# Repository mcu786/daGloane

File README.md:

daGloane
========

daGloane is a quadcopter with a takeoff mass of less than 50grams

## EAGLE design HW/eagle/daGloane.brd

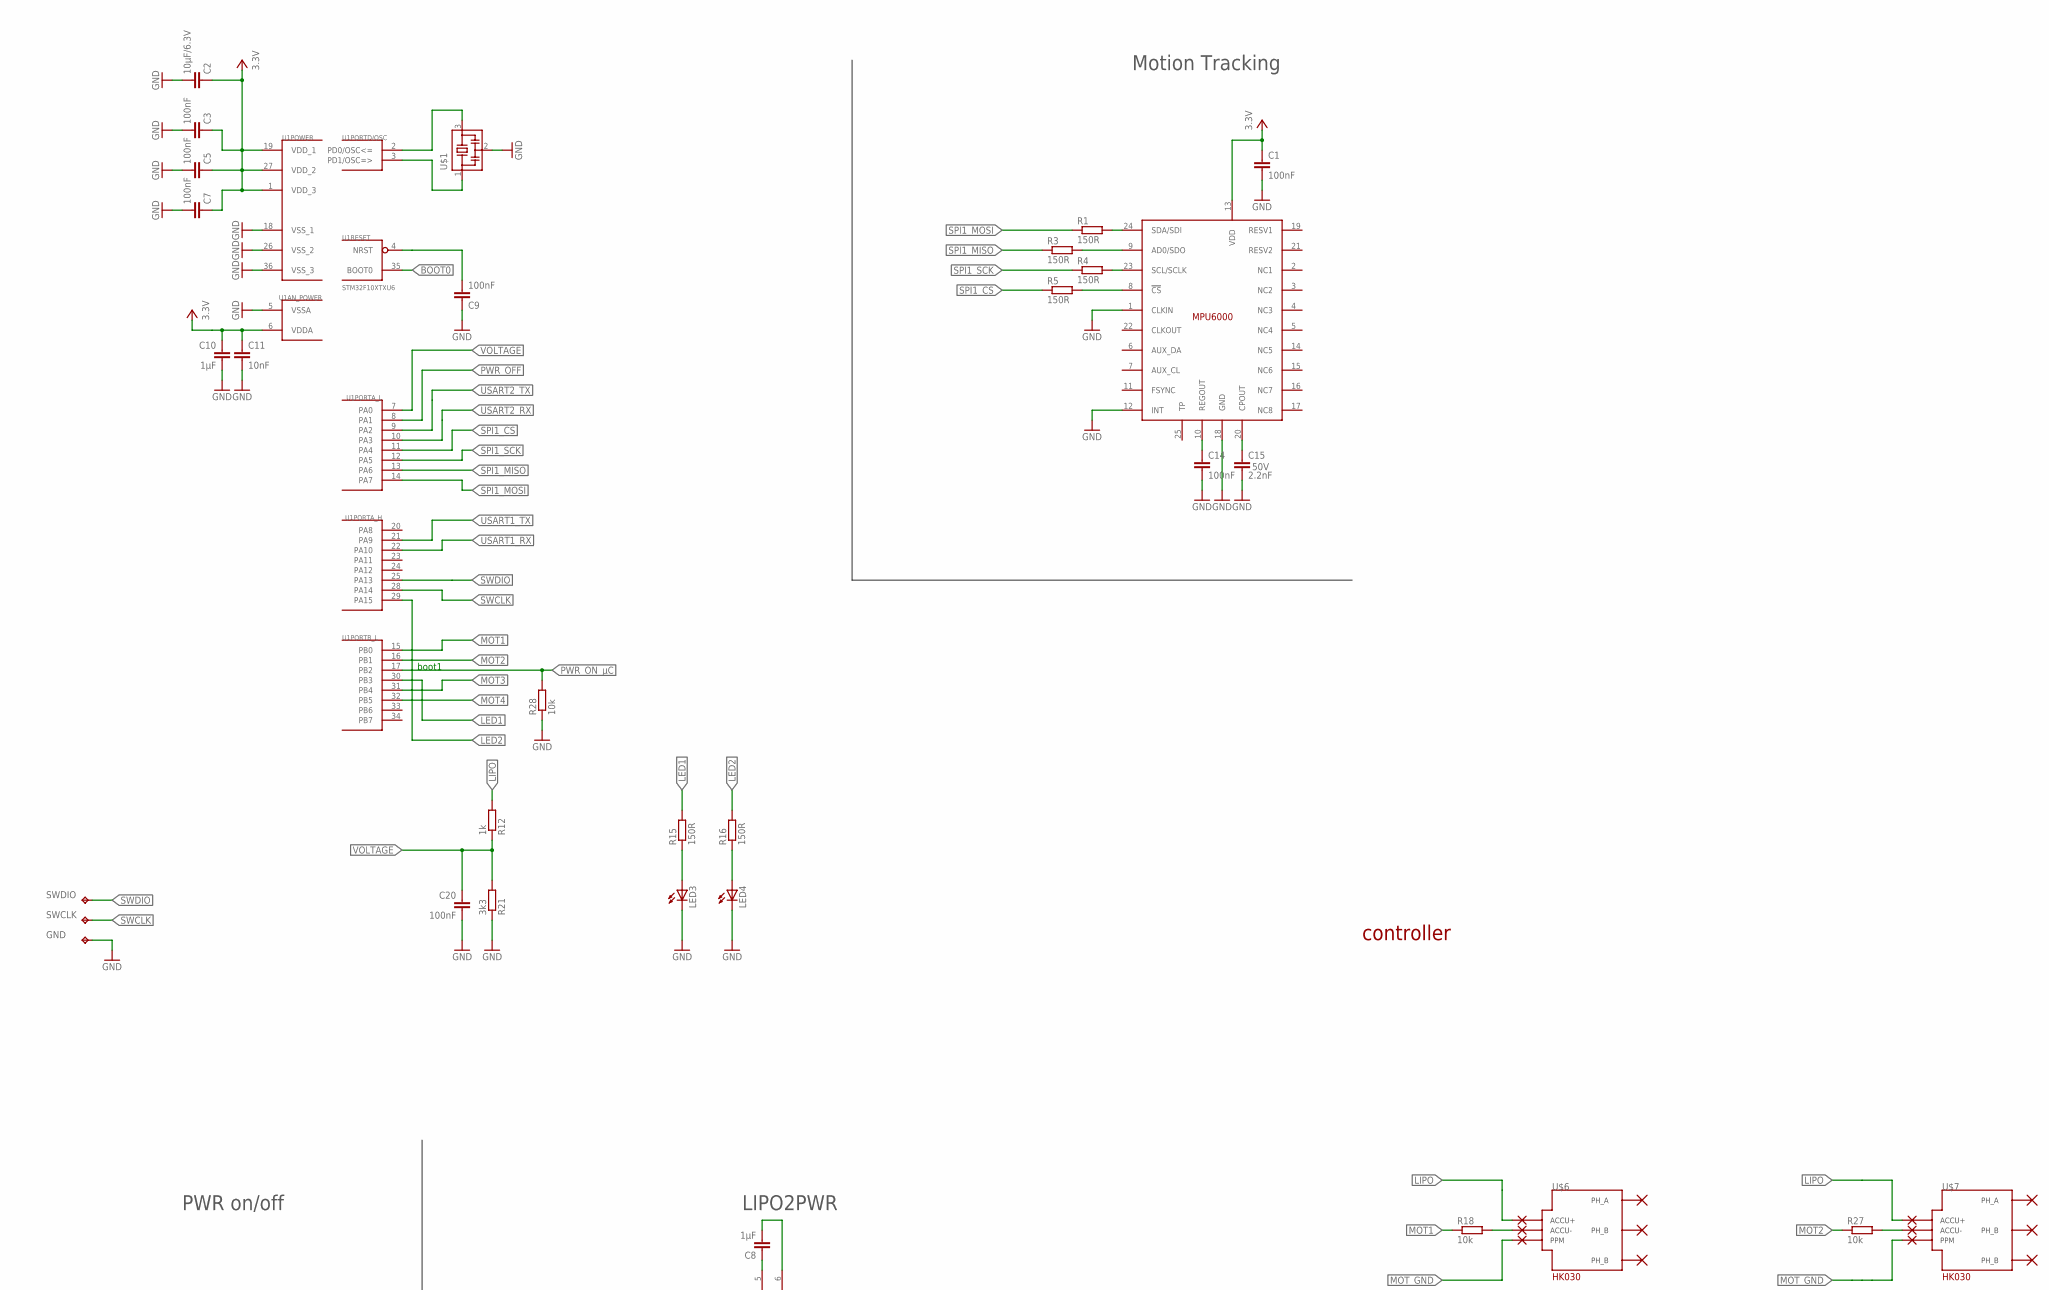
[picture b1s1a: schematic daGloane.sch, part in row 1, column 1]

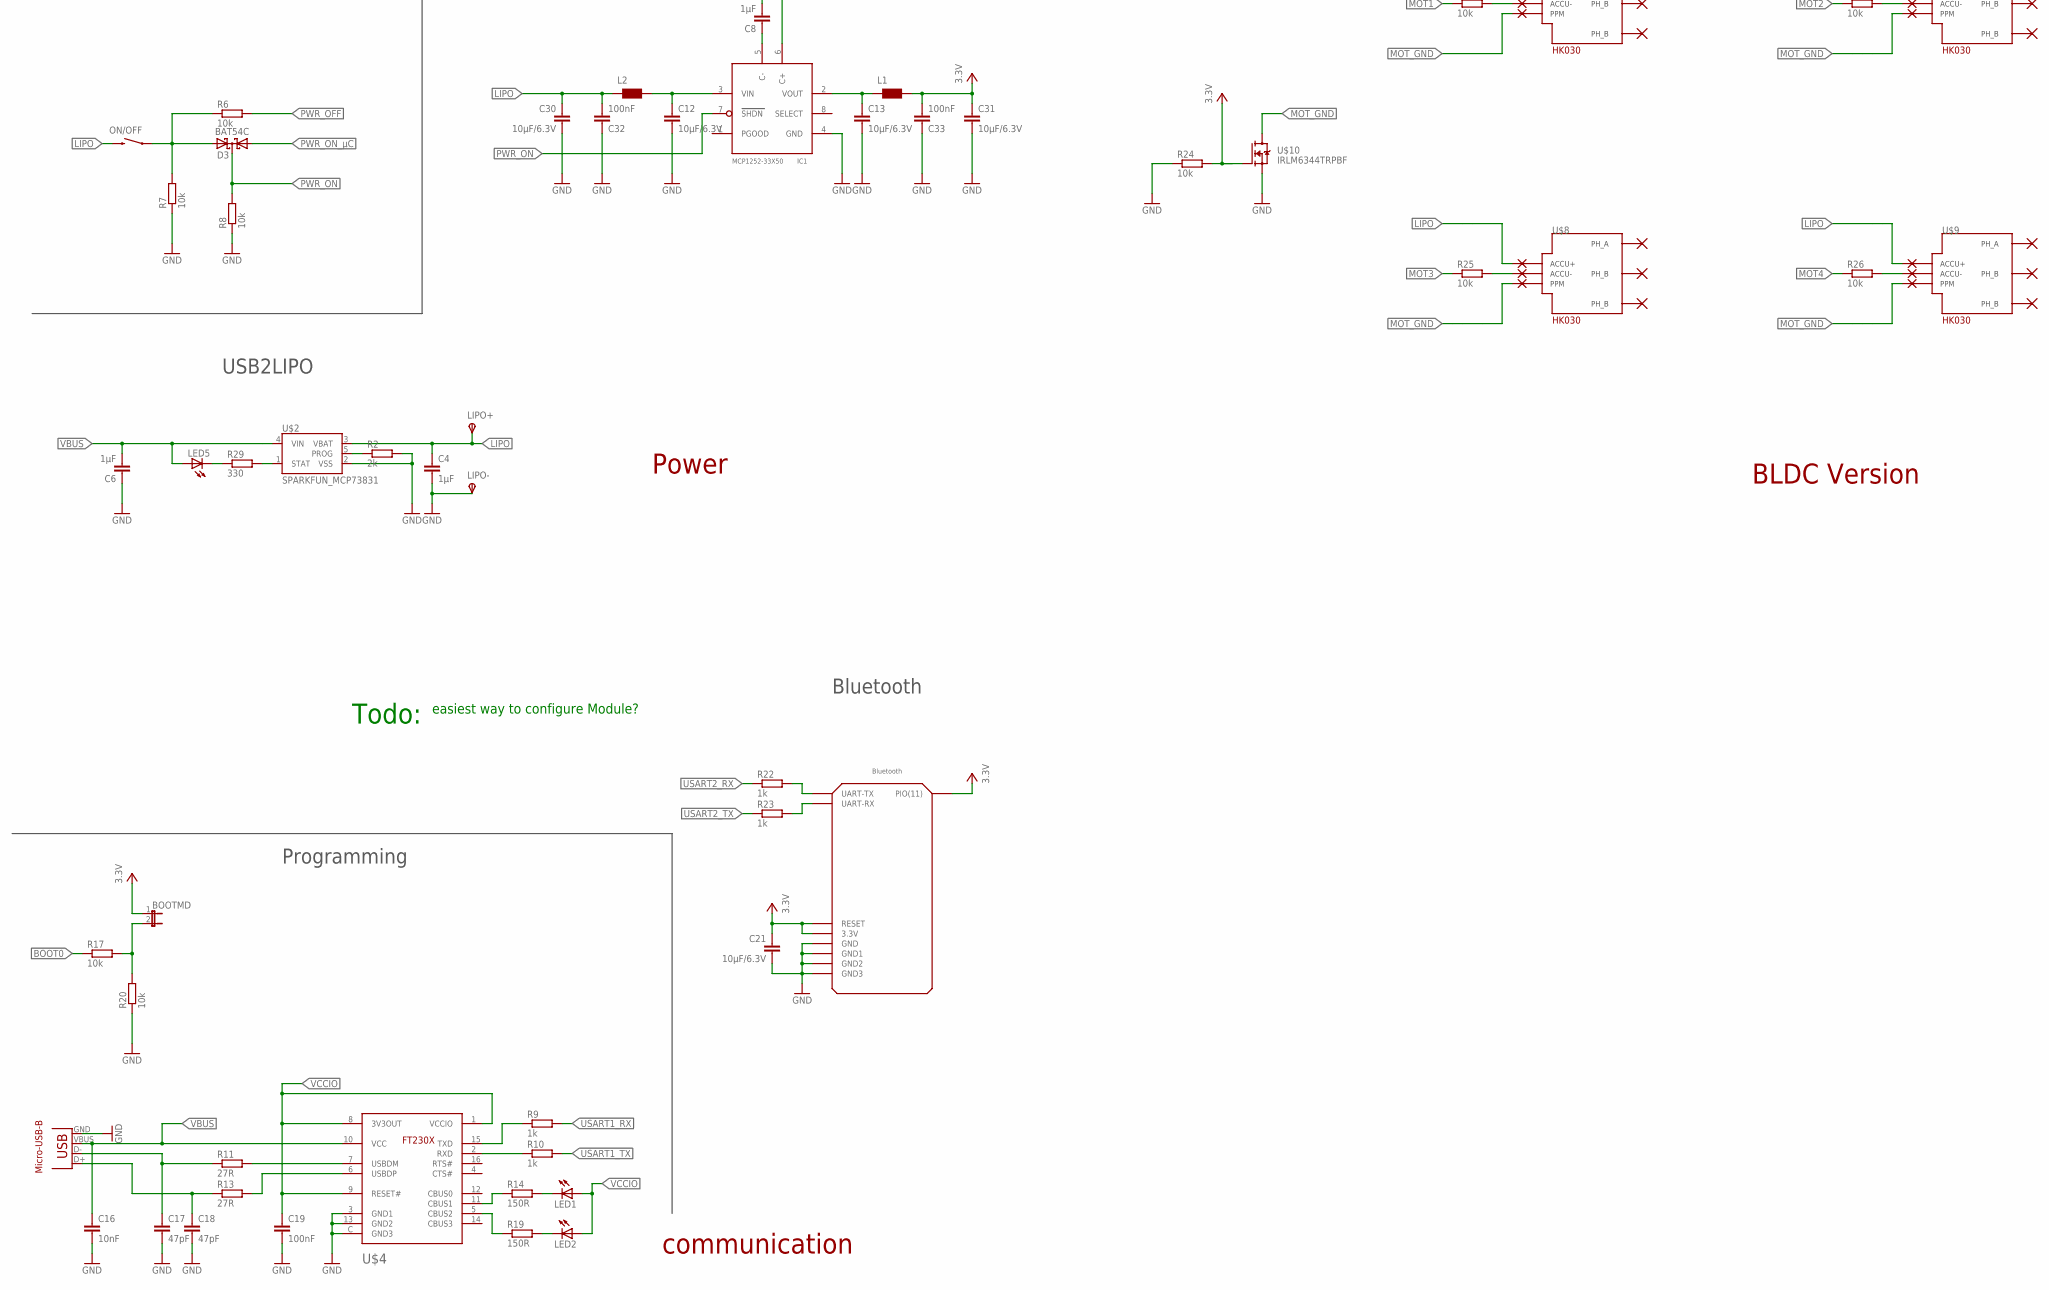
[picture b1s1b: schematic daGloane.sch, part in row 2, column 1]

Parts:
BOOTMD: JUMPER-2; 1X02_50MIL
C1, C3, C5, C7, C9, C14, C19, C20, C32, C33: 100nF; C0603
C2, C12, C13, C21, C30, C31: 10µF/6.3V; C0805
C4, C6, C8, C10: 1µF; C0603
C11, C16: 10nF; C0603
C15: 2.2nF; C0603; VOLTAGE 50V
C17, C18: 47pF; C0603
D3: BAT54C; SOT23
GND: TESTPAD_TPB1,27; TESTPAD_B1,27
IC1: MCP1252-33X50; MSOP8
L1, L2: WUERTH-ELEKTRONIK_WE-KI_0805_B
LED1, LED2, LED3, LED4, LED5: LEDCHIPLED_0603; CHIPLED_0603
LIPO+: TPSPAD1-13; P1-13
LIPO-: TPSPAD1-13; P1-13
ON/OFF: SWITCH-MOMENTARY-2SMD; TACTILE_SWITCH_SMD
PAD1, PAD2, PAD3, PAD4, PAD5, PAD6, PAD7, PAD8, PAD9, PAD10, PAD11, PAD12: SMD2; SMD1,27-2,54
R1, R3, R4, R5, R14, R15, R16, R19: 150R; R0603
R2: 2k; R0603
R6, R7, R8, R17, R18, R20, R24, R25, R26, R27, R28: 10k; R0603
R9, R10, R12, R22, R23: 1k; R0603
R11, R13: 27R; R0603
R21: 3k3; R0603
R29: 330; R0603
SWCLK: TESTPAD_TPB1,27; TESTPAD_B1,27
SWDIO: TESTPAD_TPB1,27; TESTPAD_B1,27
U1: STM32F10XTXU6; VFQFPN36
U$1: MURATA-FILTER_CSTCE__G
U$2: SPARKFUN_MCP73831; SPARKFUN_SOT23-5
U$3: MPU6000
U$4: SERIAL_FT230XQ; SERIAL_QFN4X4-16
U$5: BLUETOOTH_REDUCED
U$10: IRLM6344TRPBF; MICRO3(SOT-23)
X2: SPARKFUN-CONNECTORS_USB-MICROB

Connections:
BOOT0: R17.1, U1.35 (BOOT0)
D+: C18.1, R13.1, X2.D+
D-: C17.1, R11.1, X2.D-
GND: C1.2, C2.2, C3.2, C4.2, C5.2, C6.1, C7.2, C9.1, C10.2, C11.2, C12.2, C13.2, C14.2, C15.2, C16.2, C17.2, C18.2, C19.2, C20.2, C21.2, C30.2, C31.2, C32.1, C33.1, GND.PP, IC1.4 (GND), LED3.C, LED4.C, LIPO-.TP, R2.2, R7.1, R8.1, R20.1, R21.1, R24.1, R28.1, U1.5 (VSSA), U1.18 (VSS_1), U1.26 (VSS_2), U1.36 (VSS_3), U$1.2, U$2.2 (VSS), U$3.1 (CLKIN), U$3.12 (INT), U$3.18 (GND), U$4.3 (GND1), U$4.13 (GND2), U$4.C (GND3), U$5.P$13 (GND), U$5.P$14 (GND1), U$5.P$21 (GND2), U$5.P$22 (GND3), U$10.2 (S), X2.GND
LED1: R15.2, U1.30 (PB3)
LED2: R16.2, U1.29 (PA15)
LIPO: C4.1, C30.1, C32.2, L2.2 (1), LIPO+.TP, ON/OFF.3 (2), PAD1.1, PAD4.1, PAD7.1, PAD10.1, R12.2, U$2.3 (VBAT)
MOT1: R18.1, U1.15 (PB0)
MOT2: R27.1, U1.16 (PB1)
MOT3: R25.1, U1.31 (PB4)
MOT4: R26.1, U1.32 (PB5)
MOT_GND: PAD3.1, PAD6.1, PAD9.1, PAD12.1, U$10.3 (D)
unnamed: LED2.C, R19.2
unnamed: U1.2 (PD0/OSC<=), U$1.3
unnamed: R2.1, U$2.5 (PROG)
unnamed: R5.2, U$3.8 (!CS)
unnamed: C15.1, U$3.20 (CPOUT)
unnamed: C14.1, U$3.10 (REGOUT)
unnamed: R22.2, U$5.P$1 (UART-TX)
unnamed: LED3.A, R15.1
unnamed: LED4.A, R16.1
unnamed: BOOTMD.2, R17.2, R20.2
unnamed: R14.1, U$4.11 (CBUS1)
unnamed: R19.1, U$4.5 (CBUS2)
unnamed: R4.2, U$3.23 (SCL/SCLK)
unnamed: LED1.C, R14.2
unnamed: R23.2, U$5.P$2 (UART-RX)
unnamed: R11.2, U$4.7 (USBDM)
unnamed: R13.2, U$4.6 (USBDP)
unnamed: R3.2, U$3.9 (AD0/SDO)
unnamed: R1.2, U$3.24 (SDA/SDI)
unnamed: R9.1, U$4.15 (TXD)
unnamed: R10.1, U$4.2 (RXD)
unnamed: PAD2.1, R18.2
unnamed: D3.2 (A2), ON/OFF.1, R6.1, R7.2
unnamed: C8.2, IC1.6 (C+)
unnamed: U1.3 (PD1/OSC=>), U$1.1
unnamed: C8.1, IC1.5 (C-)
unnamed: PAD11.1, R27.2
unnamed: PAD5.1, R25.2
unnamed: PAD8.1, R26.2
unnamed: R29.2, U$2.1 (STAT)
unnamed: LED5.C, R29.1
unnamed: C12.1, IC1.3 (VIN), L2.1 (2)
unnamed: C13.1, IC1.2 (VOUT), L1.2 (1)
PWR_OFF: R6.2, U1.8 (PA1)
PWR_ON: D3.3 (CC), IC1.7 (SHDN), R8.2
PWR_ON_µC: D3.1 (A1), R28.2, U1.17 (PB2)
RESET1: C9.2, U1.4 (NRST)
SPI1_CS: R5.1, U1.11 (PA4)
SPI1_MISO: R3.1, U1.13 (PA6)
SPI1_MOSI: R1.1, U1.14 (PA7)
SPI1_SCK: R4.1, U1.12 (PA5)
SWCLK: SWCLK.PP, U1.28 (PA14)
SWDIO: SWDIO.PP, U1.25 (PA13)
USART1_RX: R9.2, U1.22 (PA10)
USART1_TX: R10.2, U1.21 (PA9)
USART2_RX: R22.1, U1.10 (PA3)
USART2_TX: R23.1, U1.9 (PA2)
VBUS: C6.2, C16.1, LED5.A, U$2.4 (VIN), U$4.10 (VCC), X2.VBUS
VCC: BOOTMD.1, C1.1, C2.1, C3.1, C5.1, C7.1, C10.1, C11.1, C21.1, C31.1, C33.2, L1.1 (2), R24.2, U1.1 (VDD_3), U1.6 (VDDA), U1.19 (VDD_1), U1.27 (VDD_2), U$3.13 (VDD), U$5.P$11 (RESET), U$5.P$12 (3.3V), U$5.P$34 (PIO(11)), U$10.1 (G)
VCCIO: C19.1, LED1.A, LED2.A, U$4.1 (VCCIO), U$4.8 (3V3OUT), U$4.9 (RESET#)
VOLTAGE: C20.1, R12.1, R21.2, U1.7 (PA0)

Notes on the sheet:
Micro-USB-B
FT230X
boot1
Power
communication
controller
Programming
Bluetooth
LIPO2PWR
USB2LIPO
PWR on/off
Motion Tracking
Todo:
easiest way to configure Module?
BLDC Version

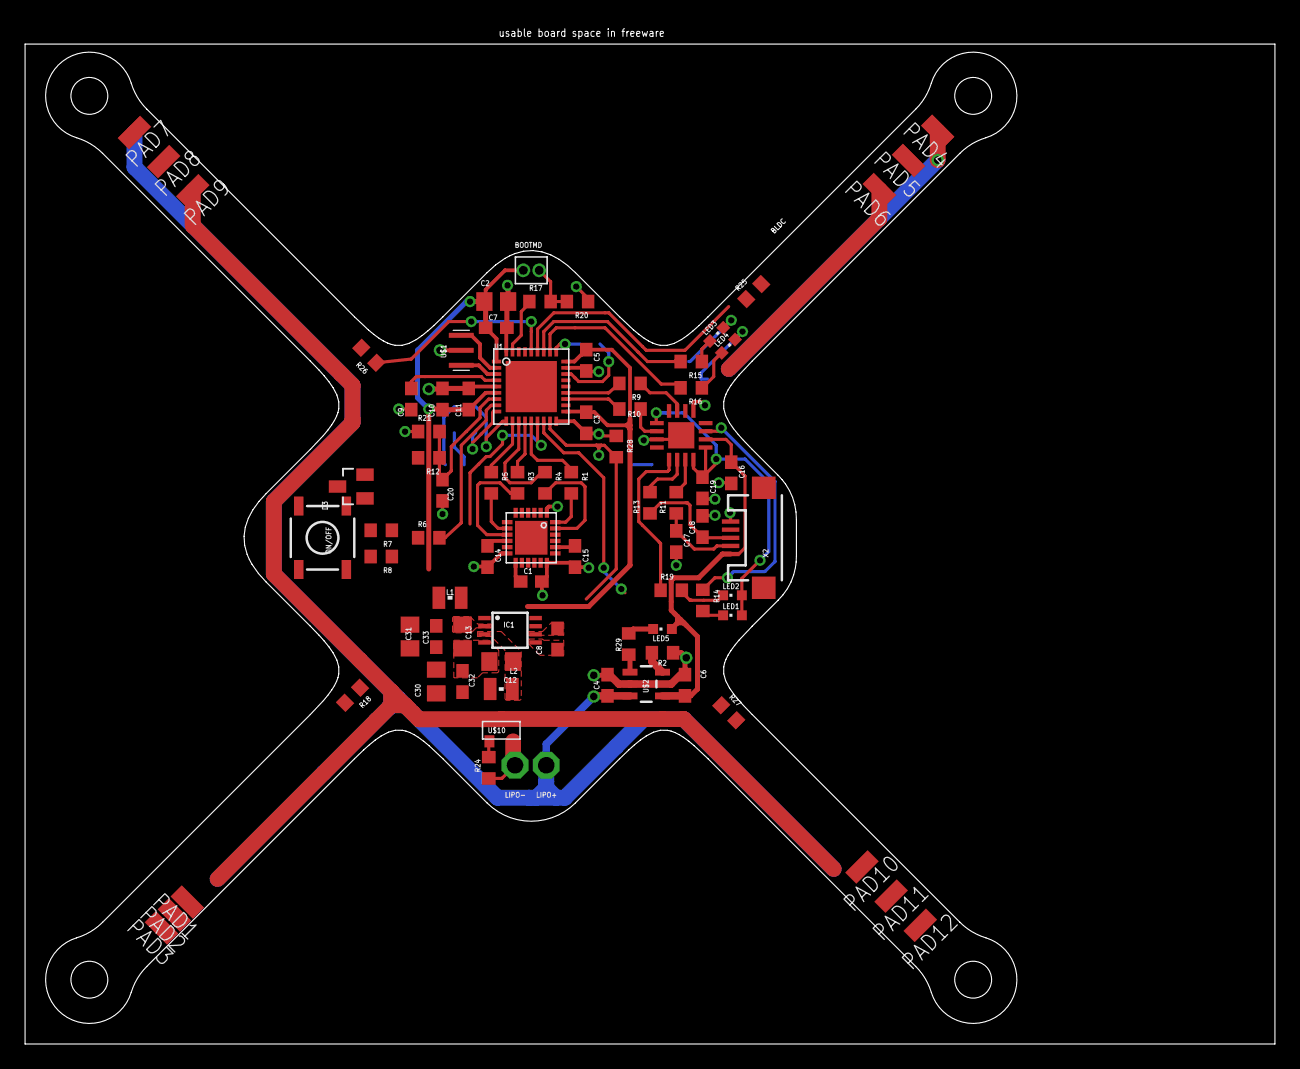
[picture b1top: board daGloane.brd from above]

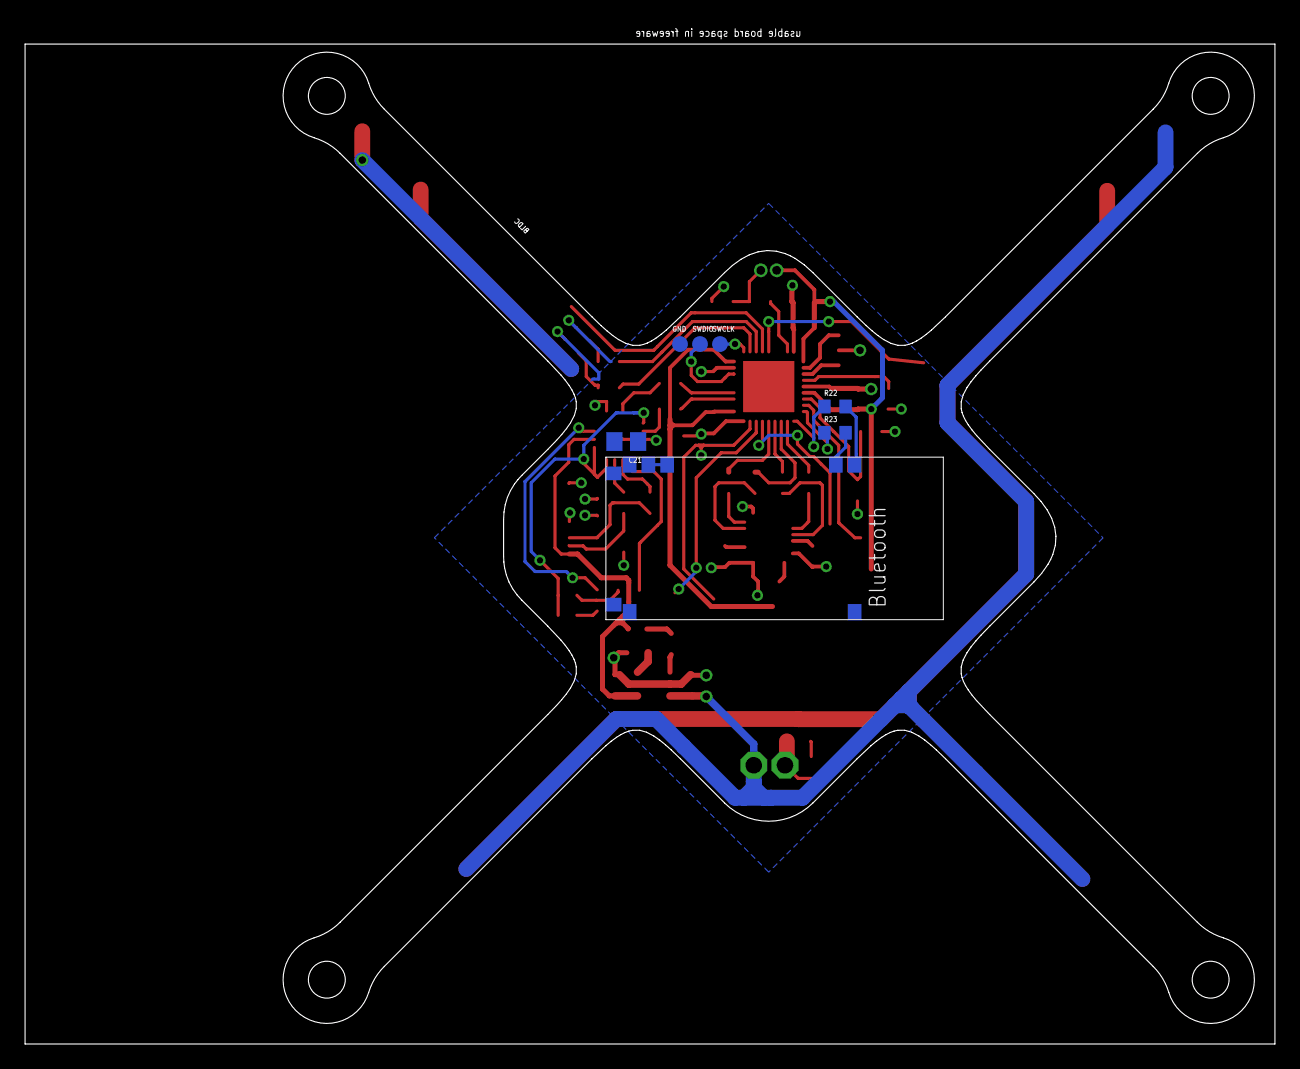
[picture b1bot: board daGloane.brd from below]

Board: 2 copper layers, 100.0 x 81.5 mm, 90 parts (7 on the bottom side), 63 nets.

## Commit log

2012-05-11 inital commit of daGloane schematic
2012-05-11 USB2UART interface replaced MPU6000 added
2012-05-12 package size of passive components reduced to 0603 dual LED replaced by standart LEDs in 0805 package
2012-05-12 -MCP1252 added: Low Noise, Positive-Regulated Charge Pump (Lipo 3..4.2V -> 3.3V) -MCP73831 added: Single Cell, Fully Integrated Li-Ion,Li-Polymer Charge Management Controller (USB Batterie Charging)
2012-05-12 tacticle switch and nesessacy circuitry for power on/off added. leakage current might become an issure..
2012-05-12 reset buttom removed.
2012-05-12 board outline imported from dxf
2012-05-12 STM32 replaced by derivate with a smaller footprint: VFQFPN36
2012-05-12 MotorPower switch added to reduce current consumption when turned off.
2012-05-13 Boad outlines for hextronik BLDC motor and X-Twin DC Motor
2012-05-13 another pcb outline added
2012-05-15 design rule check file added
2012-05-15 package outline for MPU600 package added
2012-05-17 pin assignment of µC changed pwm outputs for the motors are now on PB0,PB1,PB4 and PB5. Those I/Os can be used with TIM3
2012-05-18 gnd removed
2012-05-18 all non standart parts of daGloane are in this lib now
2012-05-18 all non standart part replaced by parts found in the daGloane.lbr library
2012-05-18 micro USB b connector added to daGloane lbr
2012-05-18 tactile switch added
2012-05-18 several parts added
2012-05-21 Added Bluetooth module
2012-05-21 lbr for Bluetooth module etc.
2012-05-21 Splitted schematic in Frames
2012-05-21 Bluetooth module added
2012-05-21 replicate entry removed
2012-05-21 schematic preview image. - it is easier to see the difference between two revision in an image of the schematic
2012-05-21 modification to the image show github feature
2012-05-21 reset to actual schematic
2012-05-21 added bluetooth
2012-05-21 inital commit
2012-05-21 missing connection uart connection to bluetooth module fixed
2012-05-21 replaced lbr file recovered; bluetooth module lib integrated in original lbr
2012-05-21 bluetooth module added- again- something went wrong before..
2012-05-21 2 descrete diodes replaced by one part containing to diodes
2012-05-22 MTD6501C brushless driver IC added to lib
2012-05-22 frame with bldc drive version added to schematic
2012-05-22 N MOSFET IRLML6344TRPbF added to lib
2012-05-22 DC motor drive added to schematic
2012-05-22 gnd connection of decoppling capacitors of BLDC motor drivers changed to mot_gnd
2012-05-23 positionering of BLDC Conectors
2012-05-23 Added Datasheets
2012-05-28 led added to LiPo charge IC
2012-05-28 we inductor added
2012-05-28 - PI filter added to charge pump DC/DC - trough hole pads for BLDC motors replaced with SMT type pads
2012-05-29 100nF capacitor added to PI filters of charge pump dc/dc series resistors of spi resized to 150R
2012-05-30 jumper package with 50mil pitch added
2012-05-30 bootmode jumper replaced with 50mil pitch type
2012-06-01 cosmetic changes
2012-06-01 brushed DC motor driver stage removed
2012-06-01 wirepad footprint added to lib
2012-06-01 wirepads for connecting the BLDC motors replaced with newly created smaller ones
2012-06-01 New outline with wider arms added. The BLDC driver ICs fit on the arms now.
2012-06-02 some pins of MC exchanged to ease layouting
2012-06-02 part positiont for layout some traces routed
2012-06-02 exchanged with proper datasheet
2012-06-02 layout
2012-06-03 minor change
2012-06-03 some routing done. 127 unrouted traces left
2012-06-03 draft outlines remove
2012-06-03 motor driver layout
2012-06-10 changed layout(usb)
2012-06-10 changed layout (usb)
2012-06-11 dummy symbol added for 3A BLDC Controller
2012-06-11 BLDC driver ICs removed dummy symbol for 3A BLDC Controllers added
2012-06-11 voltage divider layout done
2012-06-11 power-on-uC signal rewired to pin 17 of uC
2012-06-11 reduced footprint for uart only operation of bluetooth module created
2012-06-11 bluetooth module replaced with reduced pad version
2012-06-11 uart connection of bluetooth module routed
2012-07-07 FT230X layout finished BLDC power line layout started
